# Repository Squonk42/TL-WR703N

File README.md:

TL-WR703N
=========

Reverse Engineering work on the TP-LINK® TL-WR703N 150M 802.11n Wi-Fi Router

Check the http://squonk42.github.com/TL-WR703N/ web page for details.

### What?
Unlike what it is marketed for, the TP-LINK® TL-WR703N is not a “3G travel router”: it does not include a 3G modem at all, it simply means that the firmware support external USB 3G modems!

Despite this shortcoming, at less than $23, this device is the cheapest Wi-Fi router you can get west of the Pecos River! For this ridiculously low price, you get:

* A clean, small (57 mm x 57 mm x 18 mm) shiny white/light blue cover plastic case with rounded corners that is pretty easy to open with just a spudger or any other thin and resistant tool
* An Atheros AR9331 chipset with
 * An Atheros AR7040 400 MHz MIPS24kc CPU
 * Integrated 802.11n 150 Mbps (130 Mbps real) Wi-Fi with 20 dBm (100 mW) output power
* 4 MB of serial (SPI) Flash memory
* 32 MB of DDR SDRAM
* An USB 2.0 host port
* A shielded Ethernet 10/100 Mbps RJ45 jack
* An external power supply using a provided wall plug via a micro-USB socket
* A software-controlled reset pinhole switch
* A blue surface-mounted LED (that can be replaced by a 3 mm through-hole LED)
* A built-in Wi-Fi printed antenna (that can be replaced by an external one)
* An UART accessible via 2 tiny pads that provides access to the uBoot bootloader and the Linux 2.6 console

This device was released in August 2011 in China, and is not exported, though it is easy to get one on eBay.

There is also a closely related sister device as the TP-LINK® TL-MR3020 for the export market, with the following differences:

* It is CE/FCC certified
* It has 4 additional surface-mounted LEDs
* It has an additional sliding switch with 3 positions
* The reset button is combined with the WPS LED
* It has 2 Wi-Fi printed antennas, but only one is actually used
* The RJ45 Ethernet jack is not shielded
* The UART is available on a nice 0.1” pitch through-hole connector (not mounted)
* It is larger: 67 mm x 74 mm x 22 mm)
* It is more expensive: $39 on eBay

### Why?
Because of these interesting characteristics, people started to imagine unforeseen applications for the cheapest available embedded Linux platform on the market, ranging from software-only firmware customization, to hardware hacks involving fine pitch soldering in order to control various physical devices.

The manufacturer (TP-LINK) is making its best efforts to comply with the requirements of the GPL license by providing access to [sources releases of the modified GPL software used in the original firmware](http://www.tp-link.com/en/support/gpl/) (actually, those of the related [TL-MR3020 device](http://www.tp-link.com/en/support/gpl/?categoryid=547), but they are close enough). Although not useable as is, all these modifications has been ported to several existing embedded Linux distributions, and the dedicated embedded [OpenWRT distribution](https://openwrt.org/) is an excellent choice for its easy build system and support for bleeding-edge packages.

Naturally, the hardware-focused projects using the TL-WR703N tend to be centralized in a few OpenWRT forum threads ([[1]](https://forum.openwrt.org/viewtopic.php?id=36471), [[2]](https://forum.openwrt.org/viewtopic.php?id=38994), [[3]](https://forum.openwrt.org/viewtopic.php?id=39567), [[4]](https://forum.openwrt.org/viewtopic.php?id=34437), and [[5]](https://forum.openwrt.org/viewtopic.php?id=31729)), and rapidly focused on the research of available I/O resources and low-level electronic understanding. In this regard, the TL-WR703N router suffers from a complete lack of information reagarding its hardware implementation:

* The datasheet for the main chip (Atheros AR9331) is only available under NDA (Non-Disclosure Agreement)
* No available schematic, layout or BOM (Bill Of Materials) files

Although some progress has been made, like an almost exhaustive main AR9331 chip pinout and a component-by-component description, only a full reverse-engineering work can provide the answers to all the questions people will have on the TL-WR703N hardware.

So the goal of this reverse-engineering of the TP-LINK® TL-WR703N router hardware is not to reproduce the device as is, as both the main chip is not available for retail, and because it would be difficult to beat the already low prices achieved by the Chinese manufacturer anyway. But the main purpose of this work is to provide the knowledge required to fully understand the hardware of this amazing little device.

### Who?
This is the work of a single person (Michel Stempin), based on the [TP-LINK® TL-WR703N teardown](http://www.kean.com.au/oshw/WR703N/teardown/) performed by Kean from the OpenWRT forum.

### Where?
All the resulting files are available in the [corresponding GitHub repository](https://github.com/Squonk42/TL-WR703N), and discussions are taking place into the corresponding threads from the [OpenWRT forum](https://forum.openwrt.org/).

The CAD files are designed using [EagleCAD v6.10](http://www.cadsoftusa.com/eagle-pcb-design-software/?language=en). Despite the fact that the free version is limited to 2 layers only and that the boards has more layers than that, this should not be too much of a problem, as there are only a few signals located into the internal layers.

So any question, idea, remark can be posted there!

### When?
This work took around 150 hours (2 week-ends and all the evenings in-between on my spare time) to produce a first PCB layout from the raw PCB top and bottom pictures.

But spare time costs nothing, and hobbyist motivation is higher than normal paid work!

### How?
If I remember correctly, Kean took the PCB pictures using an 18 Mpx camera. Removing all borders and cleaning up the original pictures, this resulted into images of 3090 x 3210 pixels. As the PCB is approximately 1.9" x 1.9", the achieved resolution is something close to 1600 dpi, or a little bit better than a common 1200/2400 dpi flat bed scanner in one direction, worse in the other.

The drawback is that using a camera with a large depth of field, the image is not perfect. It contains:
* perspective (i.e. board edges are not parallel, and are not parallel either to the picture edges)
* a "barrel" effect due to the lens in macro mode
* pixels are not necessarily "square" in X and Y
* the actual scale is unknown

The first step was thus to clean up the picture using the perspective correction function of PS as a picture editing tool to straighten borders.

As for the other 2 next problems, the trick was to find something into these pictures that can be taken as a reference with known dimensions: the best guess was to take a large chip with numerous evenly-spaced pads, like the main AR9331 SoC U1 or the SDRAM chip U2. Using the same graphical editing program as used above, tools for correcting the lens "barrel" effect and scale differently in X and Y were used to get perfectly square pixels.

Now, both sides couldn't be directly superimposed: holes, vias and the PCB contour itself did not match correctly. A good way to fix this problem was to use PS's "puppet warp transform" tool with the 2 PCB sides on separate layers with transparency. This tool allowed to place and drag pins over the picture, so it could be stretched locally. Using this technique, it was possible to make both sides match perfectly by first placing pins at the 4 corners, then adding more pins as required until a perfect match was obtained.

At this point, 2 perfectly matched/square pictures with a resolution close to the original snapshots were available.

The last problem related to unknown scale required to perform a resize operation on these pictures, so they can be superimposed with the PCB in the ECAD software used ([EagleCAD](http://www.cadsoftusa.com/eagle-pcb-design-software/?language=en)). Again, the same chips as above were taken as references with known dimensions. Based on the datasheets, their footprint was first created into EagleCAD with exact "real" dimensions, then placed into an empty PCB file.

As I still use Windows XP, I had to use the [Glass2K](http://chime.tv/products/glass2k.shtml) utility to get either a transparent EagleCAD or picture window. Putting the EagleCAD window as large as possible on my screen, I aligned the footprint with the picture, by scaling the picture so that the round 25% picture scale was matching the EagleCAD full screen display.

By adjusting EagleCAD zoom factor from the default 1.2 to 2, it is now possible on my screen to scale the picture to 50/100/200% while zooming along with EagleCAD, and thus zoom into details "almost" easily.

That was all for the pictures, no editing any more! The drawback is that because of this last step, they are adjusted to my screen setup and cannot be shared with others easily.

The next big job was then to create all the component footprints as an EagleCAD part library. Having 2 screens helped a lot in this case, and using transparency as above, it was possible to check that the footprint was correct directly into the picture. Still, this was a tedious job. As I was doing that, I took this opportunity to also create the corresponding schematic symbols and the parts for tying the symbols and the footprints together.

Once all the parts were created, I placed them onto the PCB/picture as accurately as possible, then started to route all traces in between. There was a trick to integrate existing vias into a trace: I had to get info on the via to find its signal name, then name the trace using the same name, so they both belong to the same signal. Also, when there was only a single signal pad to connect to a via, I had to artificially add a dummy part to first create a ratsnet between 2 pads, get via info/name the ratsnest as explained, then destroy the dummy part...

I used a 1 mm/0.05 mm grid, and only a few different trace widths. However, I had to create 2 signal "classes" with different clearance values to create the correct ground/power planes.

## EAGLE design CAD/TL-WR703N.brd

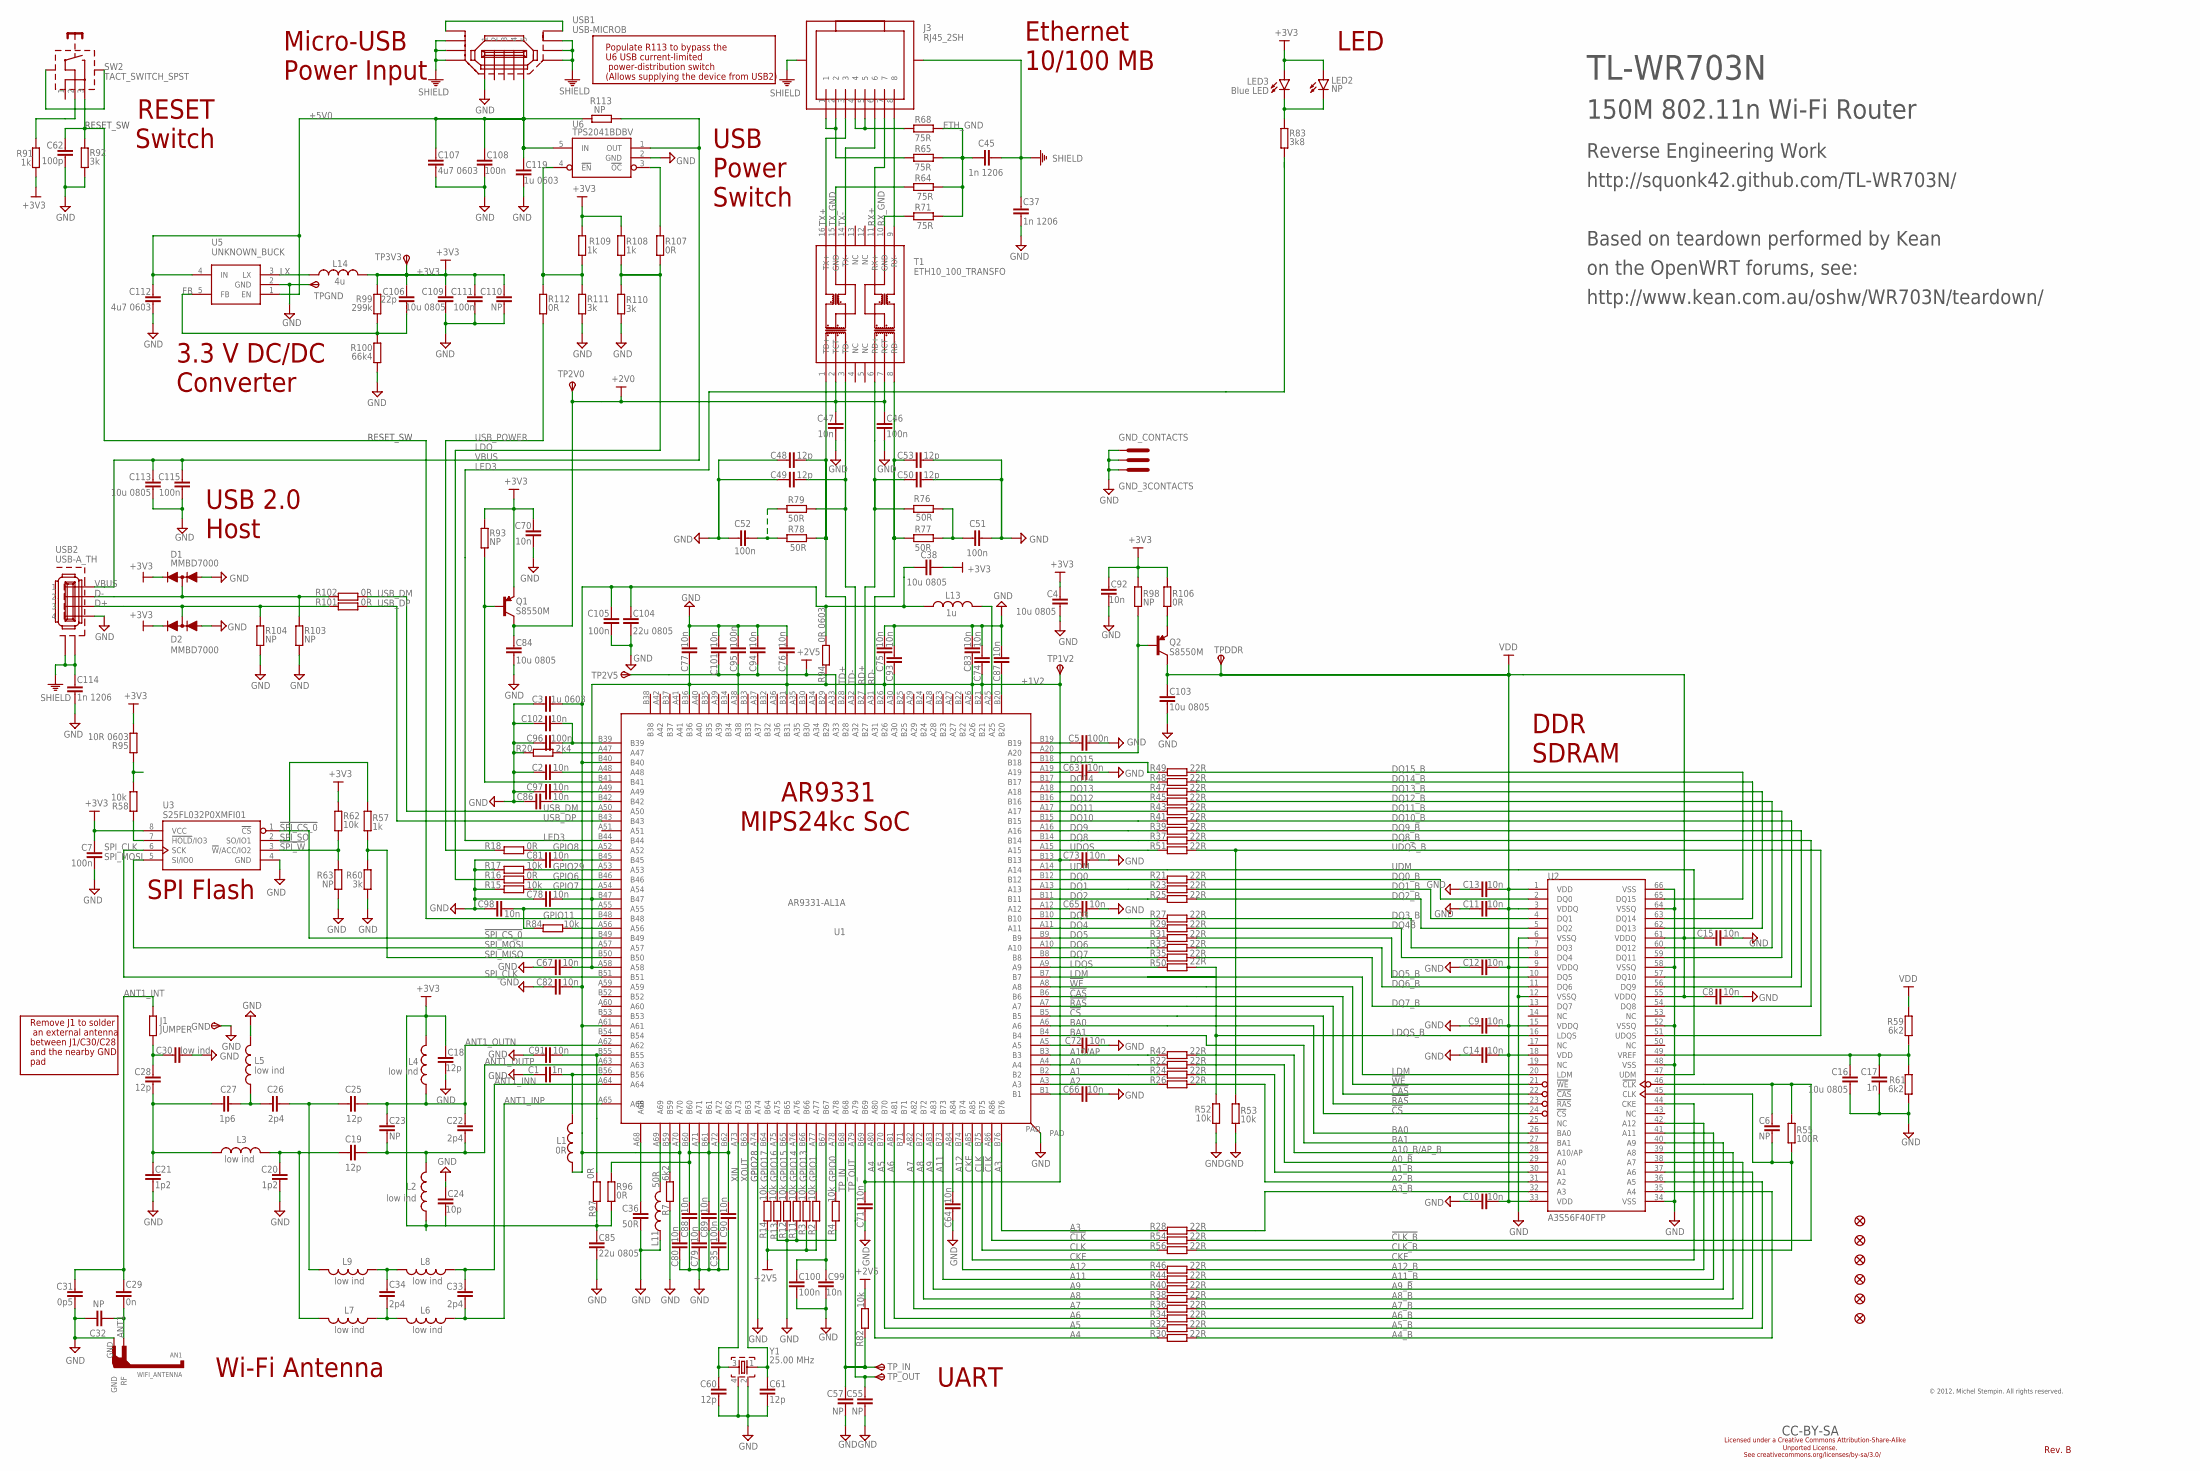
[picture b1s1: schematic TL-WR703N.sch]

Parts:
AN1: WIFI_ANTENNA
C1, C17: 1n; C0402
C2, C8, C9, C10, C11, C12, C13, C14, C15, C47, C63, C64, C65, C66, C67, C70, C71, C72, C73, C74, C75, C76, C77, C78, C79, C80, C81, C82, C83, C86, C87, C88, C89, C90, C91, C92, C93, C94, C97, C98, C99, C101, C102: 10n; C0402
C3, C119: 1u 0603; C0603
C4, C16, C38, C84, C103, C109, C113: 10u 0805; C0805
C5, C7, C35, C46, C51, C52, C95, C96, C100, C105, C108, C111, C115: 100n; C0402
C6, C23, C32, C55, C57: NP; C0402
C18, C19, C25, C28, C48, C49, C50, C53, C60, C61: 12p; C0402
C20, C21: 1p2; C0402
C22, C26, C33, C34: 2p4; C0402
C24: 10p; C0402
C27: 1p6; C0402
C29: 0n; C0402
C30: low ind; C0402
C31: 0p5; C0402
C36: 50R; C0402
C37, C45, C114: 1n 1206; C1206
C62: 100p; C0402
C85, C104: 22u 0805; C0805
C106: 22p; C0402
C107, C112: 4u7 0603; C0603
C110: NP; C0603
D1, D2: MMBD7000; SOT23-3
E$1, E$2, E$3, E$4, E$5, E$6: FIDUCIAL
E$7: CC-BY-SA
GND: TEST_PAD_SHIELD; SHIELD_PAD
GND_CONTACTS: GND_3CONTACTS; GND_3CONTACT
J1: JUMPER; J0603
J3: RJ45_2SH; RJ45_LP_RA_SMT
L1: 0R; L0402
L2, L3, L4, L5, L6, L7, L8, L9: low ind; L0402
L11: 50R; L0402
L13: 1u; L1008
L14: 4u; FERRITE_SELF
LED2: NP; LED3MM
LED3: Blue LED; LED0603
Q1, Q2: S8550M; SOT23-3
R2, R3, R4, R11, R12, R13, R14, R15, R17, R52, R53, R58, R62, R82, R84: 10k; R0402
R7, R59, R61: 6k2; R0402
R16, R18, R96, R97, R101, R102, R106, R107, R112: 0R; R0402
R20: 2k4; R0402
R21, R22, R23, R24, R25, R26, R27, R28, R29, R30, R31, R32, R33, R34, R35, R36, R37, R38, R39, R40, R41, R42, R43, R44, R45, R46, R47, R48, R49, R50, R51, R54, R56: 22R; R0402
R55: 100R; R0402
R57, R91, R108, R109: 1k; R0402
R60, R92, R110, R111: 3k; R0402
R63, R93, R98, R103, R104: NP; R0402
R64, R65, R68, R71: 75R; R0402
R76, R77, R78, R79: 50R; R0402
R83: 3k8; R0402
R94: 0R 0603; R0603
R95: 10R 0603; R0603
R99: 299k; R0402
R100: 66k4; R0402
R113: NP; R0805
SW2: TACT_SWITCH_SPST; TACT_SWITCH_SPST_RA_SMT
T1: ETH10_100_TRANSFO; H1601CG
TP1V2, TP2V0, TP2V5, TP3V3: TEST_PAD
TPDDR: TEST_PAD
TPGND: TEST_PAD
TP_IN: TEST_PAD
TP_OUT: TEST_PAD
U1: AR9331-AL1A; DRMLF164
U2: A3S56F40FTP; TSOP66
U3: S25FL032P0XMFI01; SOP8
U5: UNKNOWN_BUCK; SOT23-5
U6: TPS2041BDBV; SOT23-5
USB1: USB-MICROB
USB2: USB-A_TH
Y1: 25.00 MHz; CRYSTAL_32_25

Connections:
!CAS: U1.B6, U2.22 (!CAS)
!CLK: R54.1, U1.A86
!CLK_B: C6.2, R54.2, R55.2, U2.46 (!CLK)
!CS: U1.B5, U2.24 (!CS)
!RAS: U1.A7, U2.23 (!RAS)
!SPI_CS_0: U1.B49, U3.1 (!CS)
!SPI_W: R62.2, R63.1, U3.3 (!W!/ACC/IO2)
!WE: U1.A8, U2.21 (!WE)
$28: C52.2, R78.1, R79.2
+1V2: C67.2, C71.2, C73.1, C74.2, C75.1, C76.1, C77.2, C78.2, C83.1, R94.2, TP1V2.1, U1.A26, U1.A58, U1.B13, U1.B21, U1.B26, U1.B31, U1.B36, U1.B47, U1.B69
+2V0: C46.1, C47.1, C84.2, Q1.3 (C), T1.2 (TCT), T1.7 (RCT), TP2V0.1
+2V5: C94.2, C95.2, C101.2, R2.1, R3.1, R14.2, R82.1, TP2V5.1, U1.A33, U1.A38
+3V3: C4.2, C7.1, C18.1, C24.1, C38.2, C70.2, C85.2, C92.2, C106.2, C109.2, C110.1, C111.1, D1.2 (C), D2.2 (C), L2.1, L4.2, L14.1, LED2.A, LED3.A, Q1.2 (E), R62.1, R91.1, R93.2, R95.1, R96.2, R97.2, R98.2, R99.2, R106.2, R108.2, R109.1, TP3V3.1, U3.8 (VCC)
+5V0: C107.2, C108.2, C112.1, C119.1, R113.1, U5.1 (EN), U5.4 (IN), U6.5 (IN), USB1.VBUS (5)
A0: R22.1, U1.A4
A0_B: R22.2, U2.29 (A0)
A1: R24.1, U1.B2
A1_B: R24.2, U2.30 (A1)
A2: R26.1, U1.A3
A2_B: R26.2, U2.31 (A2)
A3: R28.1, U1.B76
A3_B: R28.2, U2.32 (A3)
A4: R30.1, U1.A80
A4_B: R30.2, U2.35 (A4)
A5: R32.1, U1.B70
A5_B: R32.2, U2.36 (A5)
A6: R34.1, U1.A81
A6_B: R34.2, U2.37 (A6)
A7: R36.1, U1.A82
A7_B: R36.2, U2.38 (A7)
A8: R38.1, U1.B72
A8_B: R38.2, U2.39 (A8)
A9: R40.1, U1.A83
A9_B: R40.2, U2.40 (A9)
A10/AP: R42.1, U1.B3
A10_B/AP_B: R42.2, U2.28 (A10/AP)
A11: R44.1, U1.B73
A11_B: R44.2, U2.41 (A11)
A12: R46.1, U1.B74
A12_B: R46.2, U2.42 (A12)
ANT1: AN1.RF, C29.2, C32.2
ANT1_INN: C33.2, L8.1, U1.A64
ANT1_INP: C33.1, L6.1, U1.A65
ANT1_INT: C29.1, C31.1, J1.2
ANT1_OUTN: C22.2, C23.2, C25.2, L4.1, U1.A62
ANT1_OUTP: C19.2, C22.1, C23.1, L2.2, U1.A63
BA0: U1.A6, U2.26 (BA0)
BA1: U1.B4, U2.27 (BA1)
CKE: U1.A85, U2.44 (CKE)
CLK: R56.1, U1.B75
CLK_B: C6.1, R55.1, R56.2, U2.45 (CLK)
D+: D2.3 (M), R101.1, R104.1, USB2.3
D-: D1.3 (M), R102.1, R103.1, USB2.2
DQ0: R21.2, U1.B12
DQ0_B: R21.1, U2.2 (DQ0)
DQ1: R23.2, U1.A13
DQ1_B: R23.1, U2.4 (DQ1)
DQ2: R25.2, U1.B11
DQ2_B: R25.1, U2.5 (DQ2)
DQ3: R27.2, U1.B10
DQ3_B: R27.1, U2.7 (DQ3)
DQ4: R29.2, U1.A11
DQ4B: R29.1, U2.8 (DQ4)
DQ5: R31.2, U1.B9
DQ5_B: R31.1, U2.10 (DQ5)
DQ6: R33.2, U1.A10
DQ6_B: R33.1, U2.11 (DQ6)
DQ7: R35.2, U1.B8
DQ7_B: R35.1, U2.13 (DQ7)
DQ8: R37.1, U1.B14
DQ8_B: R37.2, U2.54 (DQ8)
DQ9: R39.1, U1.A16
DQ9_B: R39.2, U2.56 (DQ9)
DQ10: R41.1, U1.B15
DQ10_B: R41.2, U2.57 (DQ10)
DQ11: R43.1, U1.A17
DQ11_B: R43.2, U2.59 (DQ11)
DQ12: R45.1, U1.B16
DQ12_B: R45.2, U2.60 (DQ12)
DQ13: R47.1, U1.A18
DQ13_B: R47.2, U2.62 (DQ13)
DQ14: R48.1, U1.B17
DQ14_B: R48.2, U2.63 (DQ14)
DQ15: R49.1, U1.B18
DQ15_B: R49.2, U2.65 (DQ15)
ETH_GND: C45.2, R64.1, R65.2, R68.2, R71.1
FB: C106.1, R99.1, R100.2, U5.5 (FB)
GND: AN1.GND, C1.2, C2.2, C3.2, C4.1, C5.2, C7.2, C8.2, C9.1, C10.1, C11.1, C12.1, C13.1, C14.1, C15.2, C16.1, C17.1, C18.2, C20.1, C21.1, C24.2, C30.2, C31.2, C32.1, C35.1, C36.1, C37.1, C46.2, C47.2, C48.1, C49.2, C50.1, C51.1, C52.1, C53.2, C55.2, C57.1, C60.1, C61.2, C62.1, C63.1, C64.1, C65.2, C66.1, C67.1, C70.1, C71.1, C72.1, C73.2, C74.1, C75.2, C76.2, C77.1, C78.1, C79.2, C80.2, C81.1, C82.1, C83.2, C84.1, C85.1, C86.1, C87.2, C88.2, C89.2, C90.2, C91.1, C92.1, C93.1, C94.1, C95.1, C96.1, C97.2, C98.2, C99.1, C100.1, C101.1, C102.1, C103.2, C104.2, C105.2, C107.1, C108.1, C109.1, C110.2, C111.2, C112.2, C113.1, C114.2, C115.1, C119.2, D1.1 (A), D2.1 (A), GND.1, GND_CONTACTS.GND$1, GND_CONTACTS.GND$2, GND_CONTACTS.GND$3, L5.2, L11.1, R4.2, R7.2, R11.1, R12.1, R13.2, R15.1, R17.1, R20.2, R52.2, R53.1, R60.1, R61.2, R63.2, R92.1, R100.1, R103.2, R104.2, R110.2, R111.1, TPGND.1, U1.A74, U1.PAD, U2.6 (VSSQ), U2.12 (VSSQ), U2.34 (VSS), U2.48 (VSS), U2.52 (VSSQ), U2.58 (VSSQ), U2.64 (VSSQ), U2.66 (VSS), U3.4 (GND), U5.2 (GND), U6.2 (GND), USB1.GND (1), USB2.4, Y1.2, Y1.4
GPIO0: R4.1, U1.A78
GPIO1: R2.2, U1.A77
GPIO6: R16.2, U1.B46
GPIO7: R15.2, U1.A54
GPIO8: R18.2, U1.A52
GPIO11: C62.2, R92.2, SW2.3, U1.B48
GPIO13: R3.2, U1.B66
GPIO14: R11.2, U1.A76
GPIO15: R12.2, U1.B65
GPIO16: R13.1, U1.A75
GPIO17: R14.1, U1.B64
GPIO29: R17.2, U1.A53
LDM: U1.B7, U2.20 (LDM)
LDO: R16.1, R107.1, R108.1, R110.1
LDQS: R50.2, U1.A9
LDQS_B: R50.1, R52.1, U2.16 (LDQS)
LED3: R83.1, U1.B44
LX: L14.2, U5.3 (LX)
unnamed: C79.1, U1.A71
RD+: C50.2, R76.2, T1.6 (RD+), U1.B27
RD-: C53.1, R77.1, T1.8 (RD-), U1.A31
RX+: J3.7, T1.11 (RX+)
RX-: J3.8, T1.9 (RX-)
RX_GND: R71.2, T1.10 (GND)
S$15: C99.2, C100.2, U1.B67
S$17: C19.1, C20.2, L3.2, L7.2
S$18: C3.1, C38.1, C80.1, C82.2, C104.1, C105.1, L1.2, L13.1, R94.1, U1.A61, U1.A70, U1.B40
S$36: C65.1, U1.A12
S$44: C16.2, C17.2, R59.2, R61.1, U2.49 (VREF)
S$54: C51.2, R76.1, R77.2
S$55: LED2.K (C), LED3.C, R83.2
S$73: C34.1, L6.2, L7.1
S$76: C1.1, L1.1, U1.B56
S$78: R58.1, R95.2
S$80: C21.2, C27.1, C28.1, L3.1
S$87: C28.2, C30.1, J1.1
S$94: C26.1, C27.2, L5.1
S$95: R20.1, U1.A47
S$102: C86.2, U1.B42
S$103: C5.1, C87.1, U1.B19, U1.B20
S$106: R91.2, SW2.2
S$107: SW2.S$1 (SH$1), SW2.S$2 (SH$2)
S$110: USB1.P$1 (M0), USB1.P$2 (M7)
S$114: C35.2, U1.A72
S$115: L11.2, U1.A69
S$116: R7.1, U1.B59
S$117: C88.1, C89.1, C90.1, R96.1, U1.B60, U1.B61, U1.B62
S$121: C63.2, U1.A19
S$122: C81.2, U1.B45
S$125: C91.2, R97.1, U1.B55
S$127: C34.2, L8.2, L9.1
S$128: R109.2, R111.2, R112.2, U6.4 (!EN)
S$130: C25.1, C26.2, L9.2
S$133: C96.2, C102.2, U1.B39
S$135: C97.1, U1.A49
S$136: C98.1, R84.1, U1.A55
S$137: R58.2, U3.7 (!HOLD!/IO3)
S$138: R84.2, U1.A56
S$145: L13.2, U1.A25
S$152: C2.1, U1.A48
S$192: C64.2, C66.2, U1.A84, U1.B1
S$194: R107.2, U6.3 (!OC)
S$203: Q1.1 (B), R93.1, U1.B41
S$290: J3.1, J3.2, R65.1
S$291: J3.4, J3.5, R68.1
S$354: C36.2, U1.A68
S$380: Q2.2 (E), R106.1
S$409: C93.2, U1.A30
S$430: Q2.1 (B), R98.1, U1.A20
S$434: C72.2, U1.A5
SHIELD: C37.2, C45.1, C114.1, J3.S$1 (SHIELD), J3.S$2 (SHIELD), USB1.S$1 (M1), USB1.S$2 (M2), USB1.S$3 (M3), USB1.S$4 (M4), USB1.S$5 (M5), USB1.S$6 (M6), USB2.S$1 (M1), USB2.S$2 (M2)
SPI_CLK: U1.B51, U3.6 (SCK)
SPI_MISO: R57.2, R60.2, U1.B50
SPI_MOSI: U1.A57, U3.5 (SI/IO0)
SPI_SO: R57.1, U3.2 (SO/IO1)
TD+: C48.2, R78.2, T1.1 (TD+), U1.B28
TD-: C49.1, R79.1, T1.3 (TD-), U1.A32
TP_IN: C57.2, R82.2, TP_IN.1, U1.B68
TP_OUT: C55.1, TP_OUT.1, U1.A79
TX+: J3.3, T1.16 (TX+)
TX-: J3.6, T1.14 (TX-)
TX_GND: R64.2, T1.15 (GND)
UDM: U1.A14, U2.47 (UDM)
UDQS: R51.1, U1.A15
UDQS_B: R51.2, R53.2, U2.51 (UDQS)
USB_DM: R102.2, U1.A50
USB_DP: R101.2, U1.B43
USB_POWER: R18.1, R112.1
VBUS: C113.2, C115.2, R113.2, U6.1 (OUT), USB2.1
VDD: C8.1, C9.2, C10.2, C11.2, C12.2, C13.2, C14.2, C15.1, C103.1, Q2.3 (C), R59.1, TPDDR.1, U2.1 (VDD), U2.3 (VDDQ), U2.9 (VDDQ), U2.15 (VDDQ), U2.18 (VDD), U2.33 (VDD), U2.55 (VDDQ), U2.61 (VDDQ)
XIN: C60.2, U1.A73, Y1.3
XOUT: C61.1, U1.B63, Y1.1

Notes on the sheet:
TL-WR703N
150M 802.11n Wi-Fi Router
Reverse Engineering Work
Based on teardown performed by Kean
on the OpenWRT forums, see:
http://www.kean.com.au/oshw/WR703N/teardown/
http://squonk42.github.com/TL-WR703N/
© 2012, Michel Stempin. All rights reserved.
CC-BY-SA
GPIO28
RESET_SW
Licensed under a Creative Commons Attribution-Share-Alike
See creativecommons.org/licenses/by-sa/3.0/
Unported License.
Rev. B
U6 USB current-limited
power-distribution switch
Populate R113 to bypass the
(Allows supplying the device from USB2)
Remove J1 to solder
an external antenna
between J1/C30/C28
and the nearby GND
pad
SPI Flash
Wi-Fi Antenna
USB 2.0
RESET
Power Input
Ethernet
LED
3.3 V DC/DC
USB
Power
Switch
AR9331
MIPS24kc SoC
Switch
SDRAM
DDR

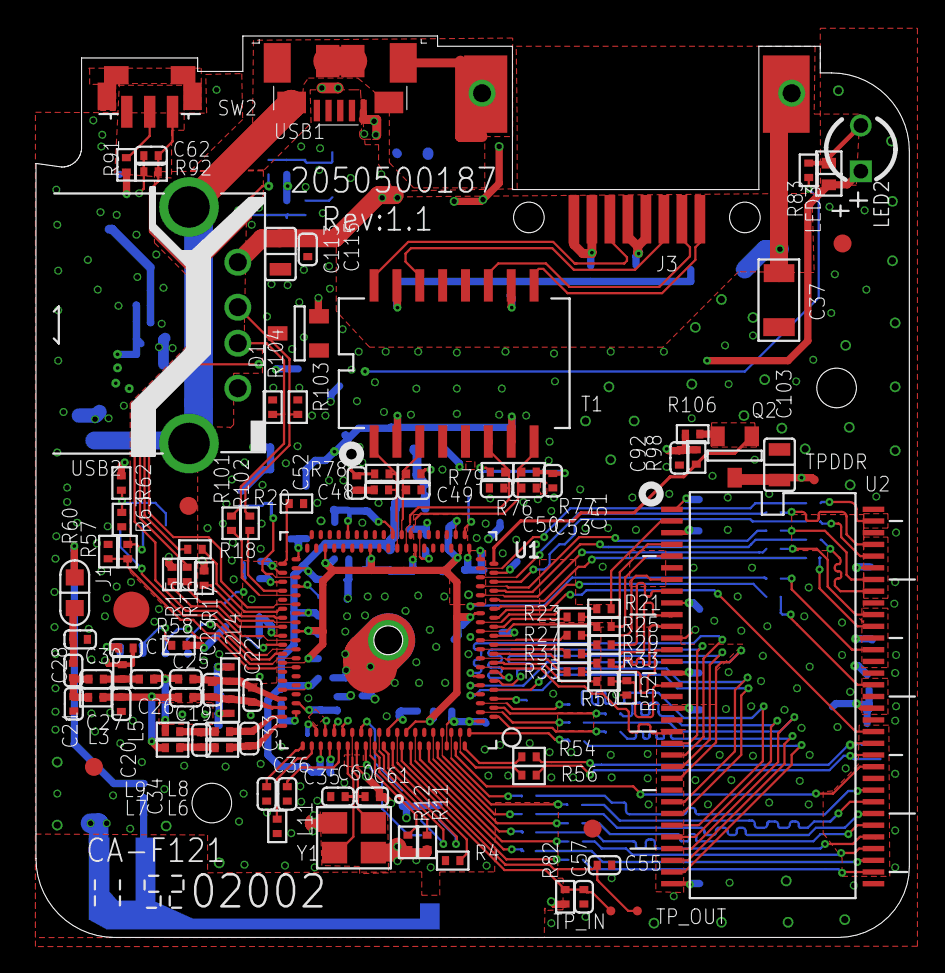
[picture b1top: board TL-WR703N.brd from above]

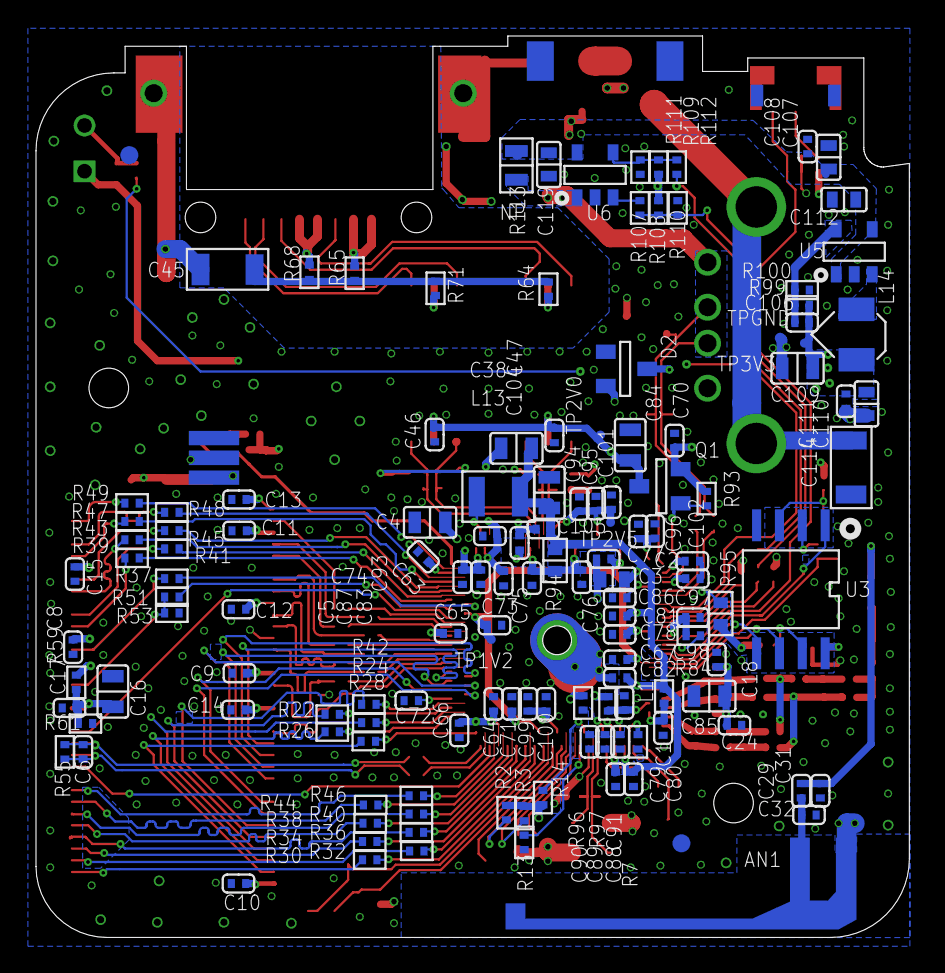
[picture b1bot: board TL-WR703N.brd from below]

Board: 2 copper layers, 48.5 x 50.1 mm, 241 parts (140 on the bottom side), 180 nets.

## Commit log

2012-09-16 Added initial files
    Board, library, datasheets and pictures
2012-09-16 Routed SDRAM
2012-09-16 Corrected to traces to SDRAM
2012-09-18 Almost completed traces on top side
2012-09-19 Definitely good progress on top side!
2012-09-22 Looks like the top side is done!
2012-09-30 Completed layout reverse engineering!
2012-09-30 Corrected a pin mapping in T1
2012-10-02 Create gh-pages branch via GitHub
2012-10-02 Update README.md
    Filled in the README
2012-10-02 Update index.html
    Added PayPal Donate button
2012-10-02 Update stylesheets/stylesheet.css
    Changed CSS for forms
2012-10-02 Update index.html
    Typos
2012-10-02 Update index.html
    Removed pixel
2012-10-02 Update stylesheets/stylesheet.css
    Gradient
2012-10-02 Update stylesheets/stylesheet.css
    Transparent form
2012-10-02 Update index.html
    Removed name
2012-10-04 Connected a few missing pads to GND
2012-10-04 Added Hires images
2012-10-04 Update index.html
    Added top & bottom layouts
2012-10-04 Update index.html
    Added main.js
2012-10-04 Added top & bottom layout
2012-10-04 Added JQuery
2012-10-04 probelm with JS varaibles
2012-10-04 Fixed SeaDragon image size and JS variable
2012-10-04 Changed format of bottom layout to PNG
2012-10-04 Tried to change CSS
2012-10-04 Moved "donate" form
2012-10-04 Changed TL-MR3020 price
2012-10-04 Removed img box-shadow
2012-10-04 Added Lo-Res pictures
2012-10-05 Modiied Ethernet Transfo & USB connector symbols
2012-10-05 Added mention of EagleCAD software
2012-10-05 Added "How?" section
2012-10-05 Typo
2012-10-06 Saved board before linking to schematic
2012-10-08 Rewrote the "Why?" section
2012-10-10 Added legal stuff
2012-10-10 Duplicate headers!
2012-10-10 typo: should be dBm, not dB
2012-10-12 Added schematic & update all other files
2012-10-12 Created .gitignore file
2012-10-12 Minor cleanup
2012-10-12 Updated SeaDragon pictures
2012-10-12 Changed title
2012-10-13 Added non-mirrored bottom picture
2012-10-13 Added link to web page
2012-10-14 Updated board to Rev. B
    Added missing wire between c21 and C28, and between U1-A33 and +2V5.
    Removed internal via labels after probing with a DMM
2012-10-14 Updated SeaDragon images to latest PCB
2012-12-02 Added Disqus comments
2014-06-04 Added README.md to warn against huge PNG file (issue #3)
2015-04-14 Replaced discontinued zoom.it zoomable images with plain PNG
2018-07-11 Fix README.md typo: MISP -> MIPS

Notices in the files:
CAD/TL-WR703N.brd:
Copyright © 2012, Michel Stempin, All rights reserved
Licenced under Creative Commons CC BY-SA 3.0 license.
parts and their libraries:
TL-WR703N: See creativecommons.org/licenses/by-sa/3.0/ for details.
